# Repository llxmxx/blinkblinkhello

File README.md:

# blinkblinkhello

<h6>What is this? </h6> it's a blinky board shaped like a planet, the leds are placed as the ring of the planet.

<h6>Schematic: </h6>

<h6>PCB Design: </h6>

<h6>3D View: </h6>

<h6>BoM: </h6>

| Name | Purpose | Cost Per Item (USD) | Quantity | Total (USD) | Link | Distributor |
|------|---------|---------------------|----------|-------------|------|-------------|
| PCB | to connect and support electronic components so the led can blink | 0.40 | 5 | 2.00 | | JLCPCB |

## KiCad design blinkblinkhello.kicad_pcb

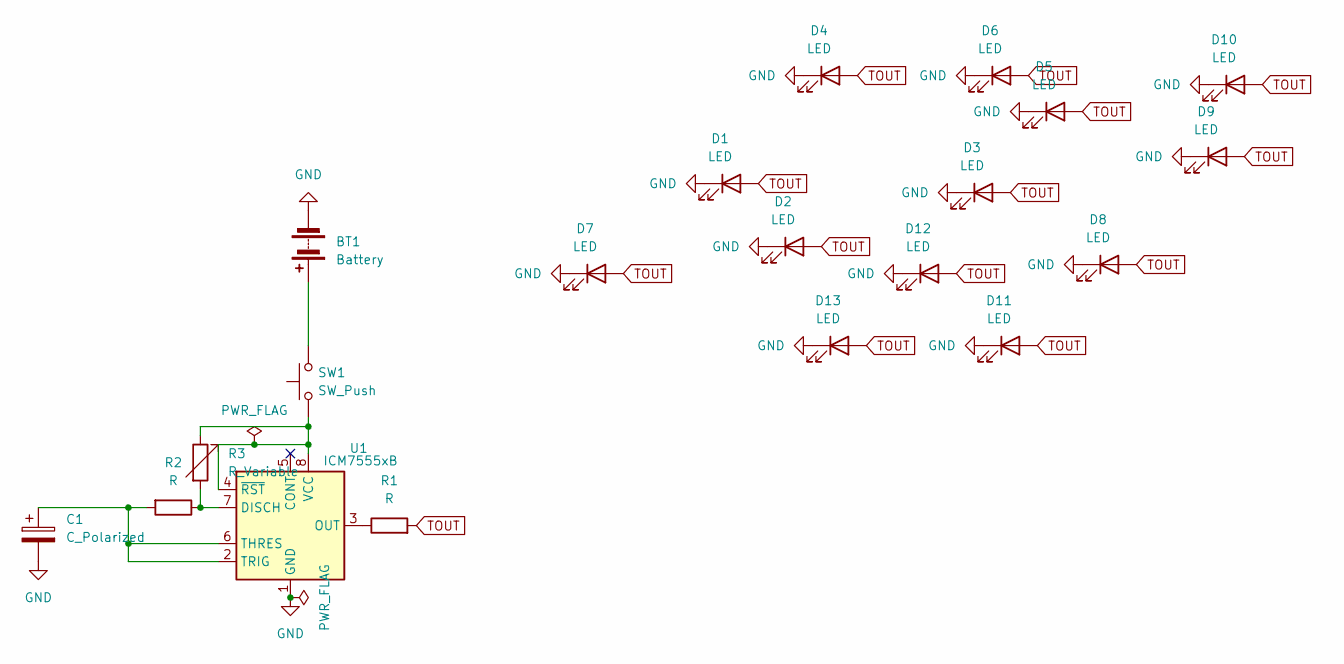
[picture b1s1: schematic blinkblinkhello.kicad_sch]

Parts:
BT1: Battery; SolderWire-0.1sqmm_1x02_P3.6mm_D0.4mm_OD1mm
C1: C_Polarized; CP_Radial_D5.0mm_P2.50mm
D1, D2, D3, D4, D5, D6, D7, D8, D9, D10, D11, D12, D13: LED; LED_D5.0mm
R1, R2: R; R_Axial_DIN0207_L6.3mm_D2.5mm_P7.62mm_Horizontal
R3: R_Variable; Potentiometer_Bourns_3386P_Vertical
SW1: SW_Push; SW_PUSH_6mm
U1: ICM7555xB; SOIC-8_3.9x4.9mm_P1.27mm

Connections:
GND: BT1.2 (-), C1.2, D1.1 (K), D2.1 (K), D3.1 (K), D4.1 (K), D5.1 (K), D6.1 (K), D7.1 (K), D8.1 (K), D9.1 (K), D10.1 (K), D11.1 (K), D12.1 (K), D13.1 (K), U1.1 (GND)
unnamed: BT1.1 (+), SW1.2
unnamed: R2.1, R3.2, U1.7 (DISCH)
unnamed: R1.1, U1.3 (OUT)
unnamed: C1.1, R2.2, U1.2 (TRIG), U1.6 (THRES)
unnamed: R3.1, SW1.1, U1.4 (~RST), U1.8 (VCC)
TOUT: D1.2 (A), D2.2 (A), D3.2 (A), D4.2 (A), D5.2 (A), D6.2 (A), D7.2 (A), D8.2 (A), D9.2 (A), D10.2 (A), D11.2 (A), D12.2 (A), D13.2 (A), R1.2

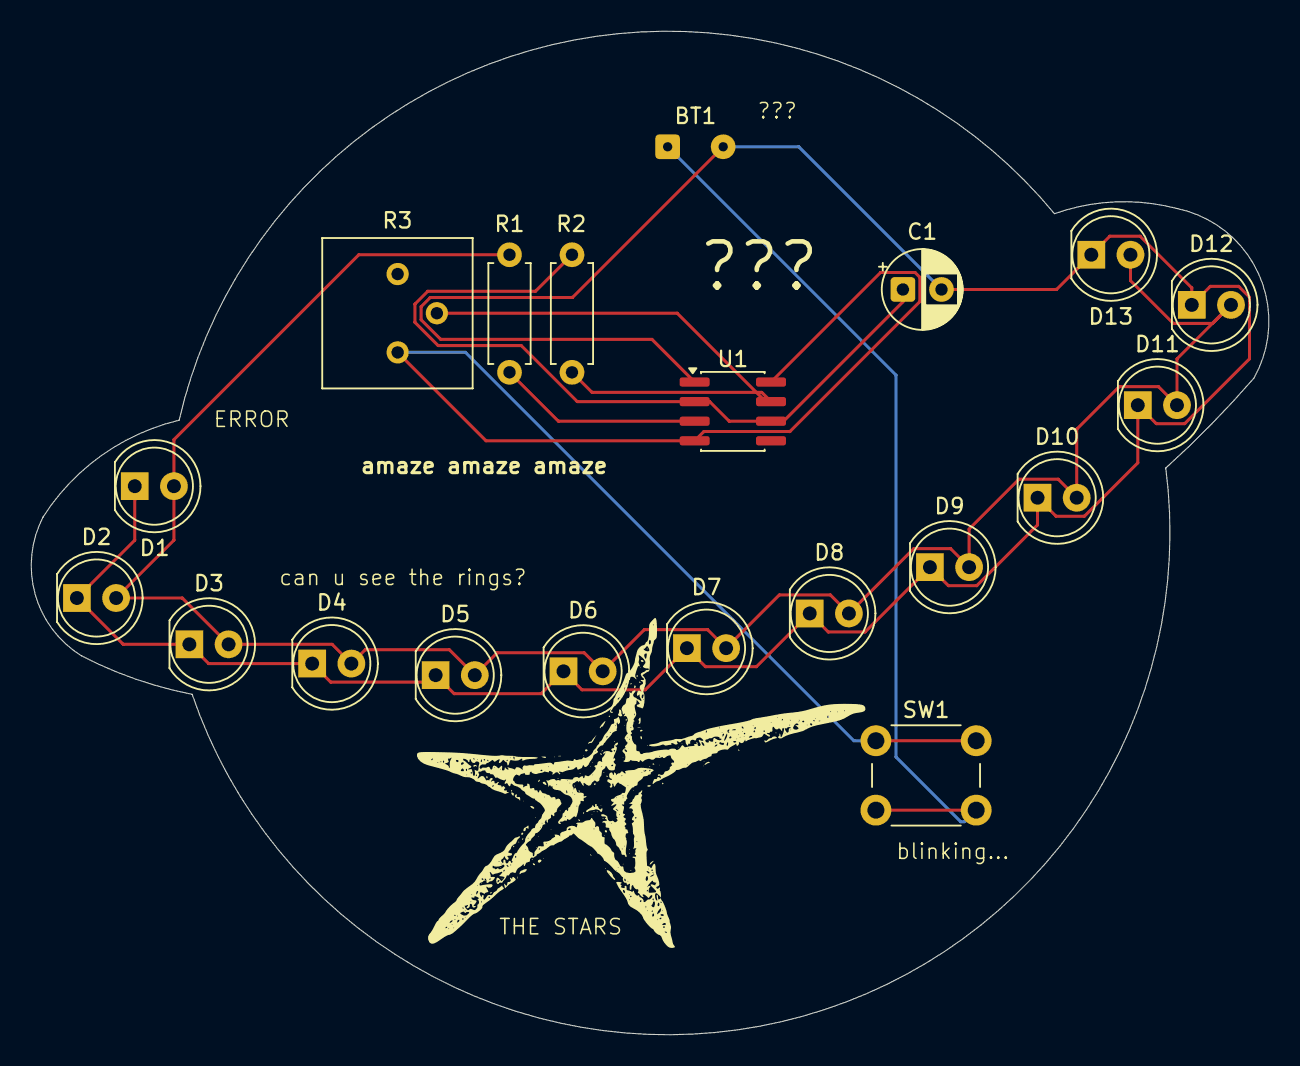
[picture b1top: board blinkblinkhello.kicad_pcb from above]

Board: 2 copper layers, 80.2 x 65.0 mm, 20 parts (0 on the bottom side), 7 nets.
